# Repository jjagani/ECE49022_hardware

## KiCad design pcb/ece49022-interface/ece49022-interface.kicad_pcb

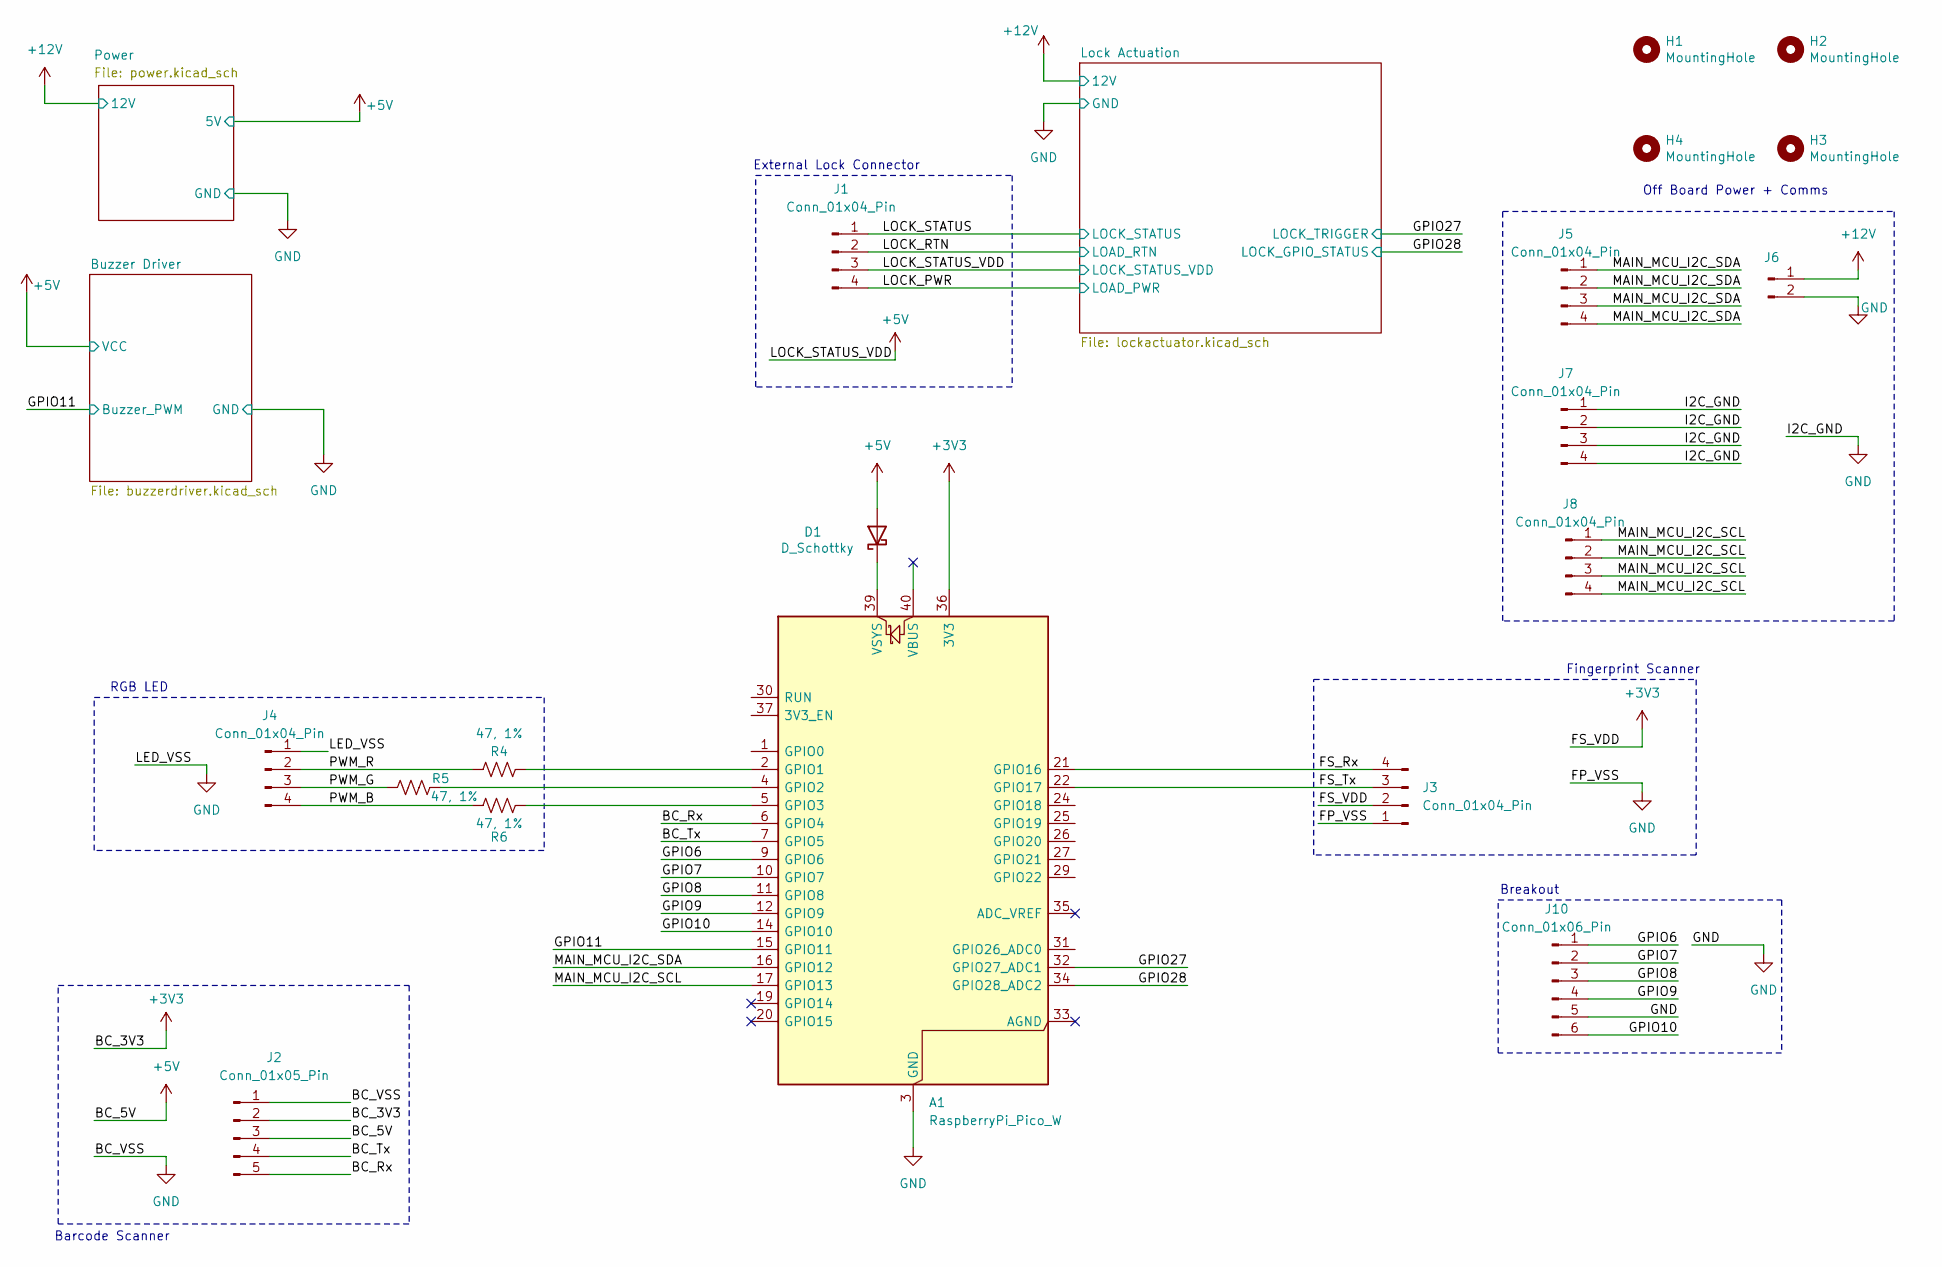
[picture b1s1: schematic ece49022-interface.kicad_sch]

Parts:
A1: RaspberryPi_Pico_W; RaspberryPi_Pico_W_SMD_HandSolder
D1: D_Schottky; D_2114_3652Metric_Pad1.85x3.75mm_HandSolder
H1, H2, H3, H4: MountingHole; MountingHole_2.7mm_M2.5
J1, J3, J4, J5, J7, J8: Conn_01x04_Pin; PinHeader_1x04_P2.54mm_Vertical
J2: Conn_01x05_Pin; PinHeader_1x05_P2.54mm_Vertical
J6: Conn_01x02_Pin; PinHeader_1x02_P2.54mm_Vertical
J10: Conn_01x06_Pin; PinHeader_1x06_P2.54mm_Vertical
R4, R5, R6: 47, 1%; R_0402_1005Metric_Pad0.72x0.64mm_HandSolder

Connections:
+3V3: A1.36 (3V3), J2.2, J3.2
+5V: D1.2 (A), J1.3, J2.3; also elsewhere on the board
+12V: J1.4, J6.1; also elsewhere on the board
/BC_Rx: A1.6 (GPIO4), J2.5
/BC_Tx: A1.7 (GPIO5), J2.4
/FS_Rx: A1.21 (GPIO16), J3.4
/FS_Tx: A1.22 (GPIO17), J3.3
/GPIO6: A1.9 (GPIO6), J10.1
/GPIO7: A1.10 (GPIO7), J10.2
/GPIO8: A1.11 (GPIO8), J10.3
/GPIO9: A1.12 (GPIO9), J10.4
/GPIO10: A1.14 (GPIO10), J10.6
/GPIO11: A1.15 (GPIO11); also elsewhere on the board
/GPIO27: A1.32 (GPIO27_ADC1); also elsewhere on the board
/GPIO28: A1.34 (GPIO28_ADC2); also elsewhere on the board
/LOCK_RTN: J1.2; also elsewhere on the board
/LOCK_STATUS: J1.1; also elsewhere on the board
/MAIN_MCU_I2C_SCL: A1.17 (GPIO13), J8.1, J8.2, J8.3, J8.4
/MAIN_MCU_I2C_SDA: A1.16 (GPIO12), J5.1, J5.2, J5.3, J5.4
/PWM_B: J4.4, R6.1
/PWM_G: J4.3, R5.1
/PWM_R: J4.2, R4.1
GND: A1.3 (GND), A1.8 (GND), A1.13 (GND), A1.18 (GND), A1.23 (GND), A1.28 (GND), A1.38 (GND), J2.1, J3.1, J4.1, J6.2, J7.1, J7.2, J7.3, J7.4, J10.5; also elsewhere on the board
unnamed: A1.2 (GPIO1), R4.2
unnamed: A1.4 (GPIO2), R5.2
unnamed: A1.5 (GPIO3), R6.2
unnamed: A1.39 (VSYS), D1.1 (K)

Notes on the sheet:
External Lock Connector
Fingerprint Scanner
Off Board Power + Comms
RGB LED
Barcode Scanner
Breakout

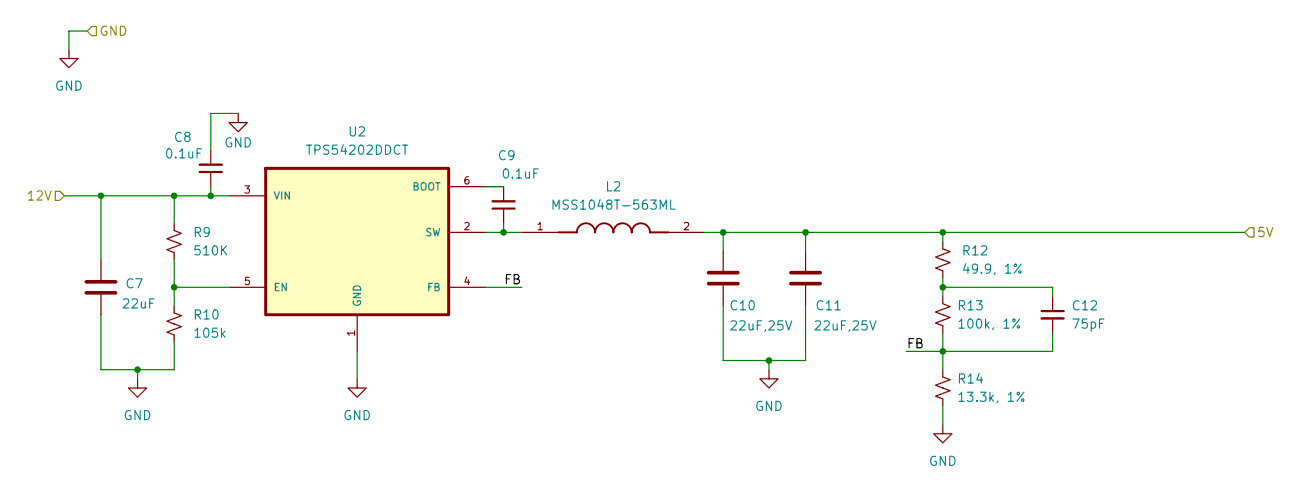
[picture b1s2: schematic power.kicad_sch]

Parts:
C7: 22uF; C_1206_3216Metric
C8, C9: 0.1uF; C_0402_1005Metric
C10, C11: 22uF,25V; C_0805_2012Metric_Pad1.18x1.45mm_HandSolder
C12: 75pF; C_0402_1005Metric
L2: MSS1048T-563ML; IND_MSS1048; PARTREV 02/16/22
R9: 510K; C_0402_1005Metric
R10: 105k; C_0402_1005Metric
R12: 49.9, 1%; C_0402_1005Metric
R13: 100k, 1%; C_0402_1005Metric
R14: 13.3k, 1%; C_0402_1005Metric
U2: TPS54202DDCT; TPS54202

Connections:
+5V: C10.1, C11.1, L2.2, R12.1; also elsewhere on the board
+12V: C7.1, C8.1, R9.1, U2.3 (VIN); also elsewhere on the board
/Power/FB: C12.2, R13.2, R14.1, U2.4 (FB)
GND: C7.2, C8.2, C10.2, C11.2, R10.2, R14.2, U2.1 (GND); also elsewhere on the board
unnamed: C12.1, R12.2, R13.1
unnamed: C9.2, U2.6 (BOOT)
unnamed: R9.2, R10.1, U2.5 (EN)
unnamed: C9.1, L2.1, U2.2 (SW)

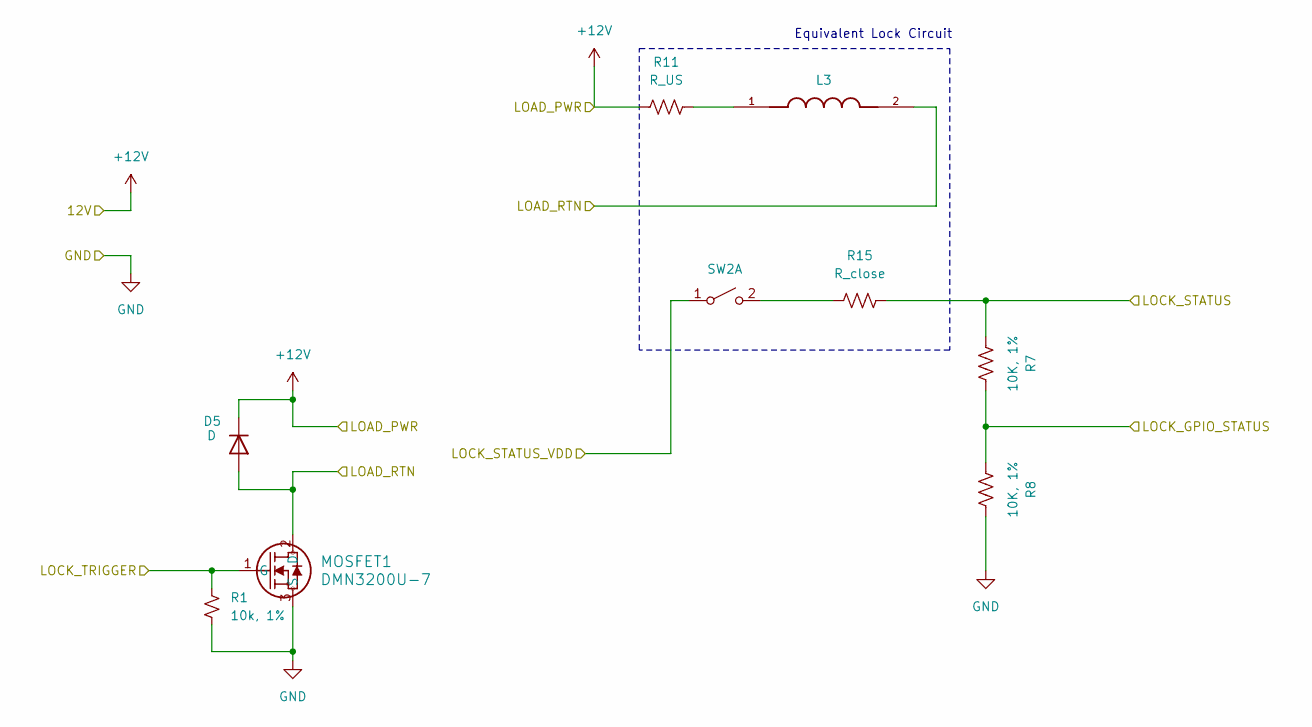
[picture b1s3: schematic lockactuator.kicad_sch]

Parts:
D5: D; SMFDO-219AB_VIS-L
L3: MSS1048T-563ML; PARTREV 02/16/22
MOSFET1: DMN3200U-7; SOT23_DMN3200U_2P9X1P3_DIO-L
R1: 10k, 1%; R_0402_1005Metric_Pad0.72x0.64mm_HandSolder
R7, R8: 10K, 1%; R_0402_1005Metric_Pad0.72x0.64mm_HandSolder
R11: R_US
R15: R_close
SW2: SW_DPST_x2

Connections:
+12V: D5.1 (K), R11.1; also elsewhere on the board
/GPIO27: MOSFET1.1 (G), R1.1; also elsewhere on the board
/GPIO28: R7.2, R8.1; also elsewhere on the board
/LOCK_RTN: D5.2 (A), L3.2, MOSFET1.2 (D); also elsewhere on the board
/LOCK_STATUS: R7.1, R15.2; also elsewhere on the board
GND: MOSFET1.3 (S), R1.2, R8.2; also elsewhere on the board
unnamed: L3.1, R11.2
unnamed: R15.1, SW2.2 (B)

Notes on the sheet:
Equivalent Lock Circuit

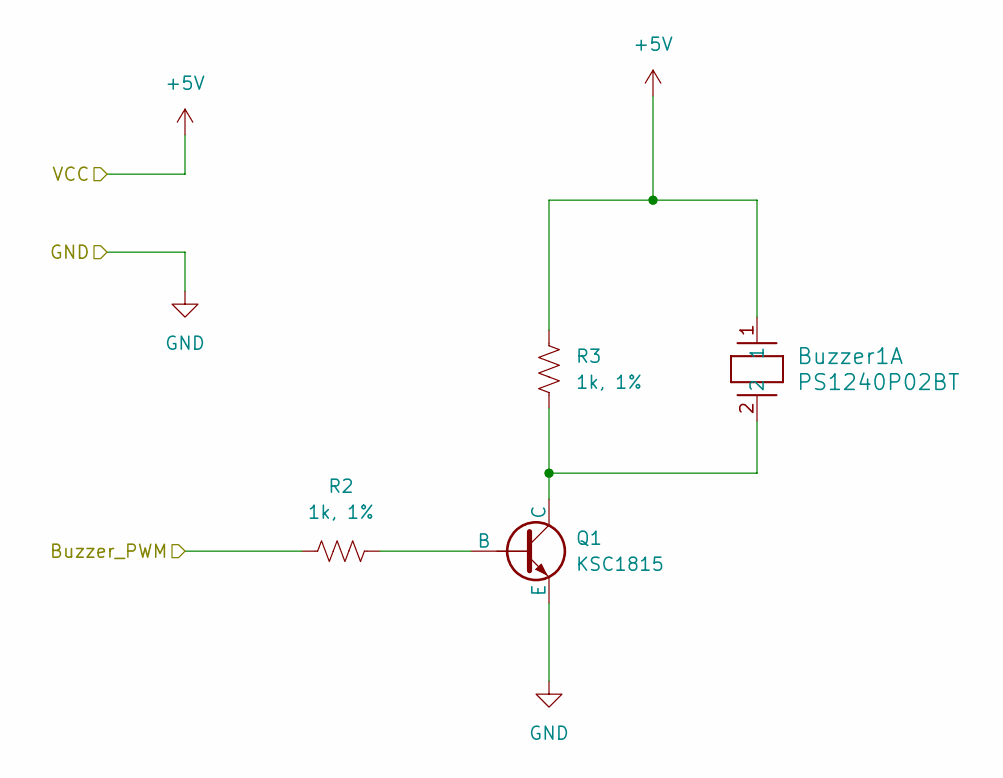
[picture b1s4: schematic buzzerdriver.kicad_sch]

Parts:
Buzzer1: PS1240P02BT; Buzzer_TDK_PS1240P02BT_D12.2mm_H6.5mm
Q1: KSC1815; TO-92L_Inline_Wide
R2, R3: 1k, 1%; R_0402_1005Metric_Pad0.72x0.64mm_HandSolder

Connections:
+5V: Buzzer1.1, R3.2; also elsewhere on the board
/GPIO11: R2.1; also elsewhere on the board
GND: Q1.3 (E); also elsewhere on the board
unnamed: Q1.2 (B), R2.2
unnamed: Buzzer1.2, Q1.1 (C), R3.1

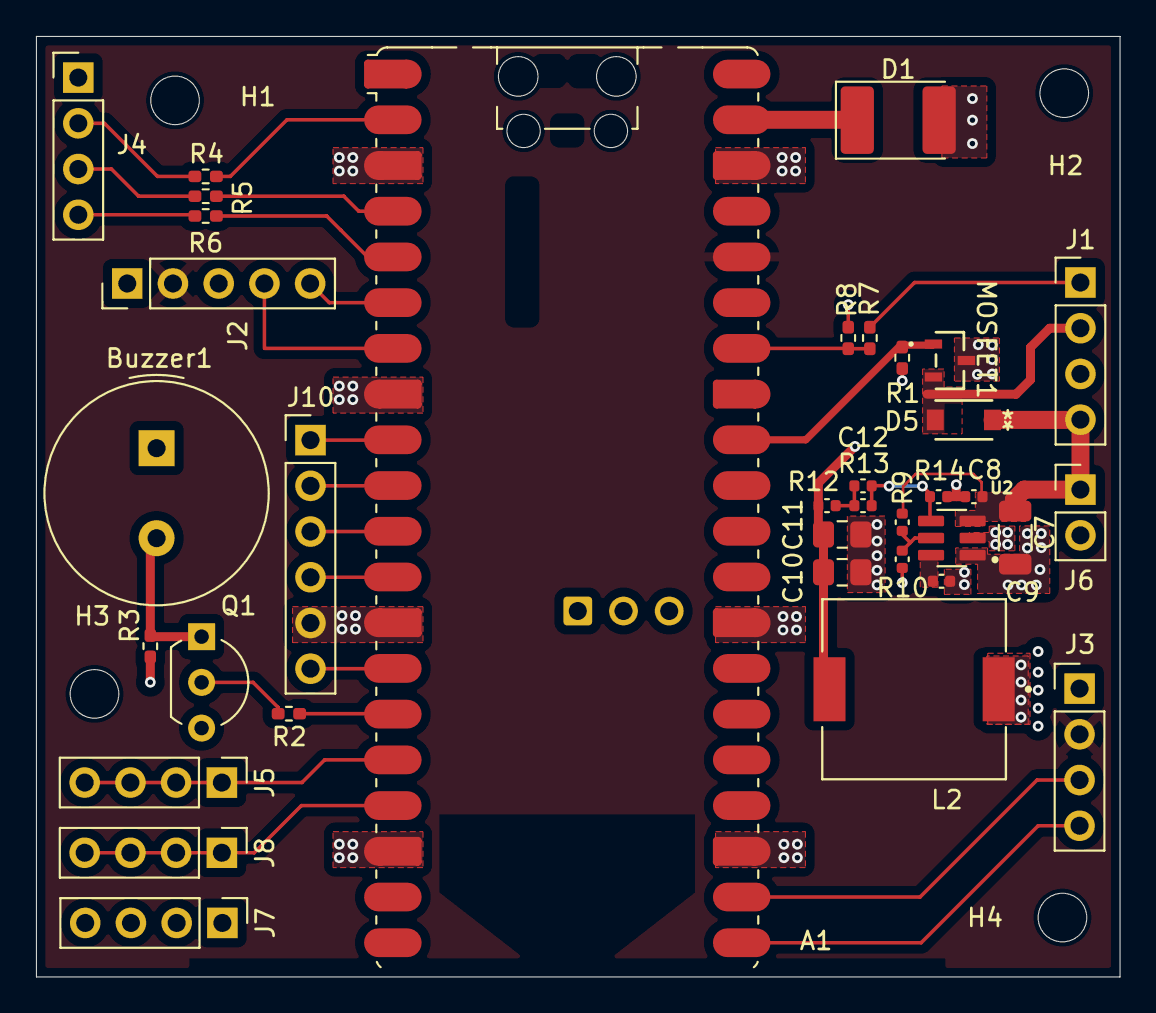
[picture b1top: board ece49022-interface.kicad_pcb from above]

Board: 4 copper layers, 60.2 x 52.2 mm, 40 parts (0 on the bottom side), 34 nets.

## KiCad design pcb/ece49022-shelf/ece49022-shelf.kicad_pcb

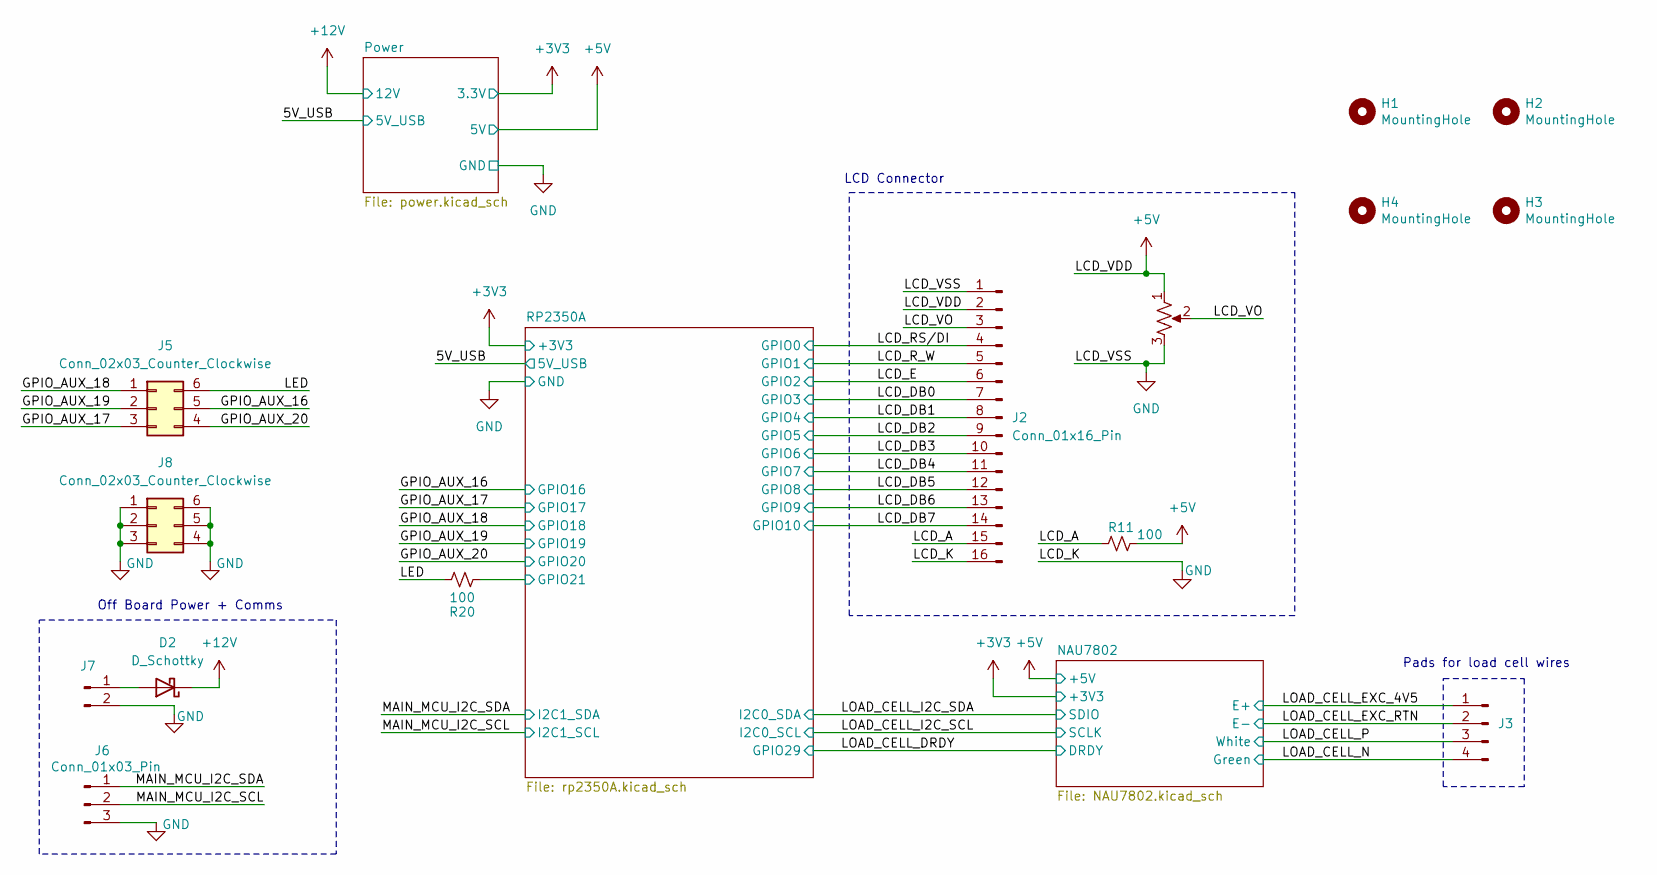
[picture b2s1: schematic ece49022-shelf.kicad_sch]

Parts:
D2: D_Schottky; SMFDO-219AB_VIS-L
H1, H2, H3, H4: MountingHole; MountingHole_2.7mm_M2.5
J2: Conn_01x16_Pin; PinSocket_1x16_P2.54mm_Vertical
J3: Conn_01x04_Pin; PinHeader_1x04_P2.54mm_Vertical
J5, J8: Conn_02x03_Counter_Clockwise; PinHeader_2x03_P2.54mm_Vertical
J6: Conn_01x03_Pin; PinHeader_1x03_P2.54mm_Vertical
J7: Conn_01x02_Pin; PinHeader_1x02_P2.54mm_Vertical
R11: 100; R_0805_2012Metric_Pad1.20x1.40mm_HandSolder
R20: 100; R_0603_1608Metric
RV1: R_Potentiometer_US; RES_C01R00

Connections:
+5V: J2.2, R11.2, RV1.1; also elsewhere on the board
+12V: D2.1 (K); also elsewhere on the board
/GPIO_AUX_16: J5.5; also elsewhere on the board
/GPIO_AUX_17: J5.3; also elsewhere on the board
/GPIO_AUX_18: J5.1; also elsewhere on the board
/GPIO_AUX_19: J5.2; also elsewhere on the board
/GPIO_AUX_20: J5.4; also elsewhere on the board
/LCD_A: J2.15, R11.1
/LCD_DB0: J2.7; also elsewhere on the board
/LCD_DB1: J2.8; also elsewhere on the board
/LCD_DB2: J2.9; also elsewhere on the board
/LCD_DB3: J2.10; also elsewhere on the board
/LCD_DB4: J2.11; also elsewhere on the board
/LCD_DB5: J2.12; also elsewhere on the board
/LCD_DB6: J2.13; also elsewhere on the board
/LCD_DB7: J2.14; also elsewhere on the board
/LCD_E: J2.6; also elsewhere on the board
/LCD_RS/DI: J2.4; also elsewhere on the board
/LCD_R_W: J2.5; also elsewhere on the board
/LCD_VO: J2.3, RV1.2
/LED: J5.6, R20.1
/LOAD_CELL_N: J3.4; also elsewhere on the board
/LOAD_CELL_P: J3.3; also elsewhere on the board
/MAIN_MCU_I2C_SCL: J6.2; also elsewhere on the board
/MAIN_MCU_I2C_SDA: J6.1; also elsewhere on the board
/RP2350A/GPIO21: R20.2; also elsewhere on the board
AVDD: J3.1; also elsewhere on the board
GND: J2.1, J2.16, J3.2, J6.3, J7.2, J8.1, J8.2, J8.3, J8.4, J8.5, J8.6, RV1.3; also elsewhere on the board
unnamed: D2.2 (A), J7.1

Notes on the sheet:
LCD Connector
Off Board Power + Comms
Pads for load cell wires

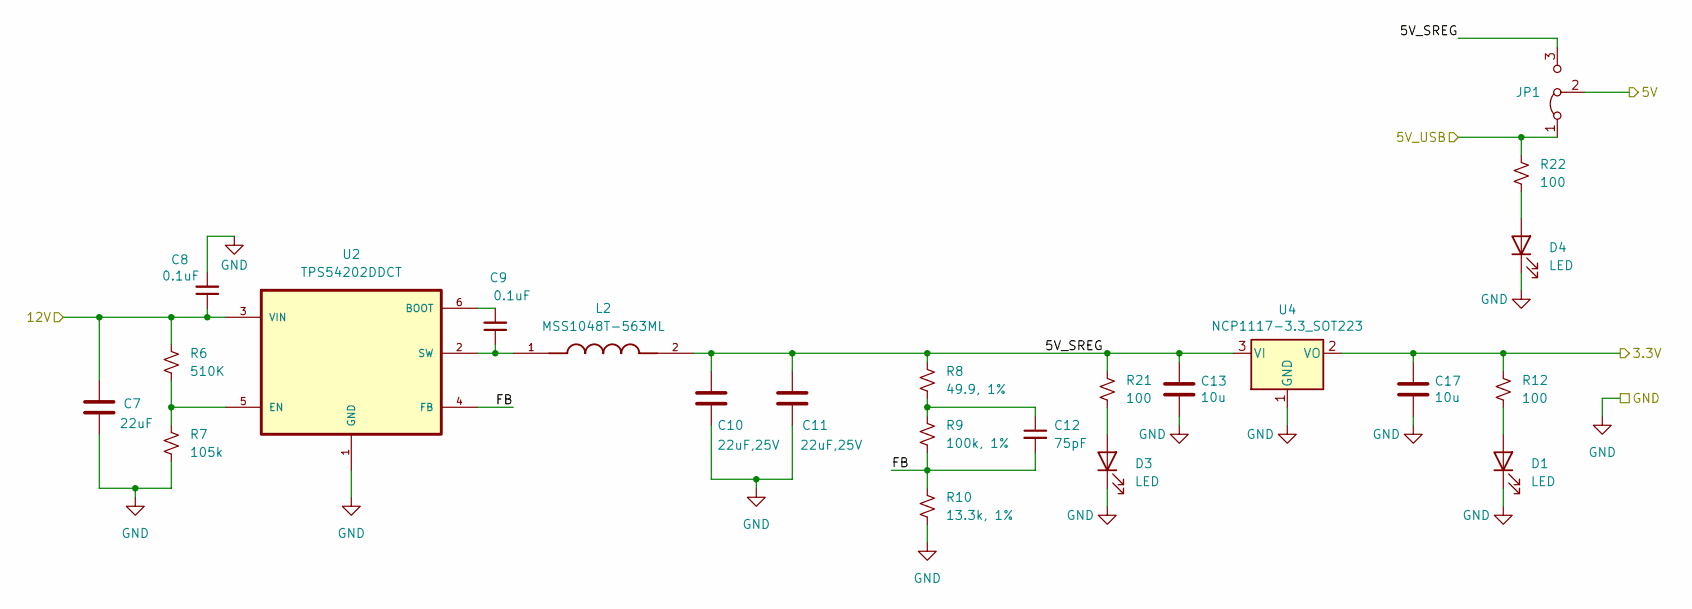
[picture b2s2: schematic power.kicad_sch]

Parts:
C7: 22uF; C_1206_3216Metric
C8, C9: 0.1uF; C_0402_1005Metric
C10, C11: 22uF,25V; C_0805_2012Metric_Pad1.18x1.45mm_HandSolder
C12: 75pF; C_0402_1005Metric
C13, C17: 10u; C_0805_2012Metric
D1, D3, D4: LED; R_0603_1608Metric
JP1: Jumper_3_Bridged12; PinHeader_1x03_P2.54mm_Vertical
L2: MSS1048T-563ML; IND_MSS1048; PARTREV 02/16/22
R6: 510K; C_0402_1005Metric
R7: 105k; C_0402_1005Metric
R8: 49.9, 1%; C_0402_1005Metric
R9: 100k, 1%; C_0402_1005Metric
R10: 13.3k, 1%; C_0402_1005Metric
R12, R21, R22: 100; R_0603_1608Metric
U2: TPS54202DDCT; TPS54202
U4: NCP1117-3.3_SOT223; SOT-223-3_TabPin2

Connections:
+3V3: C17.1, R12.1, U4.2 (VO); also elsewhere on the board
+5V: JP1.2 (C); also elsewhere on the board
+12V: C7.1, C8.1, R6.1, U2.3 (VIN); also elsewhere on the board
/5V_USB: JP1.1 (A), R22.1; also elsewhere on the board
/Power/5V_SREG: C10.1, C11.1, C13.1, JP1.3 (B), L2.2, R8.1, R21.1, U4.3 (VI)
/Power/FB: C12.2, R9.2, R10.1, U2.4 (FB)
GND: C7.2, C8.2, C10.2, C11.2, C13.2, C17.2, D1.1 (K), D3.1 (K), D4.1 (K), R7.2, R10.2, U2.1 (GND), U4.1 (GND); also elsewhere on the board
unnamed: C12.1, R8.2, R9.1
unnamed: D1.2 (A), R12.2
unnamed: D3.2 (A), R21.2
unnamed: D4.2 (A), R22.2
unnamed: C9.2, U2.6 (BOOT)
unnamed: R6.2, R7.1, U2.5 (EN)
unnamed: C9.1, L2.1, U2.2 (SW)

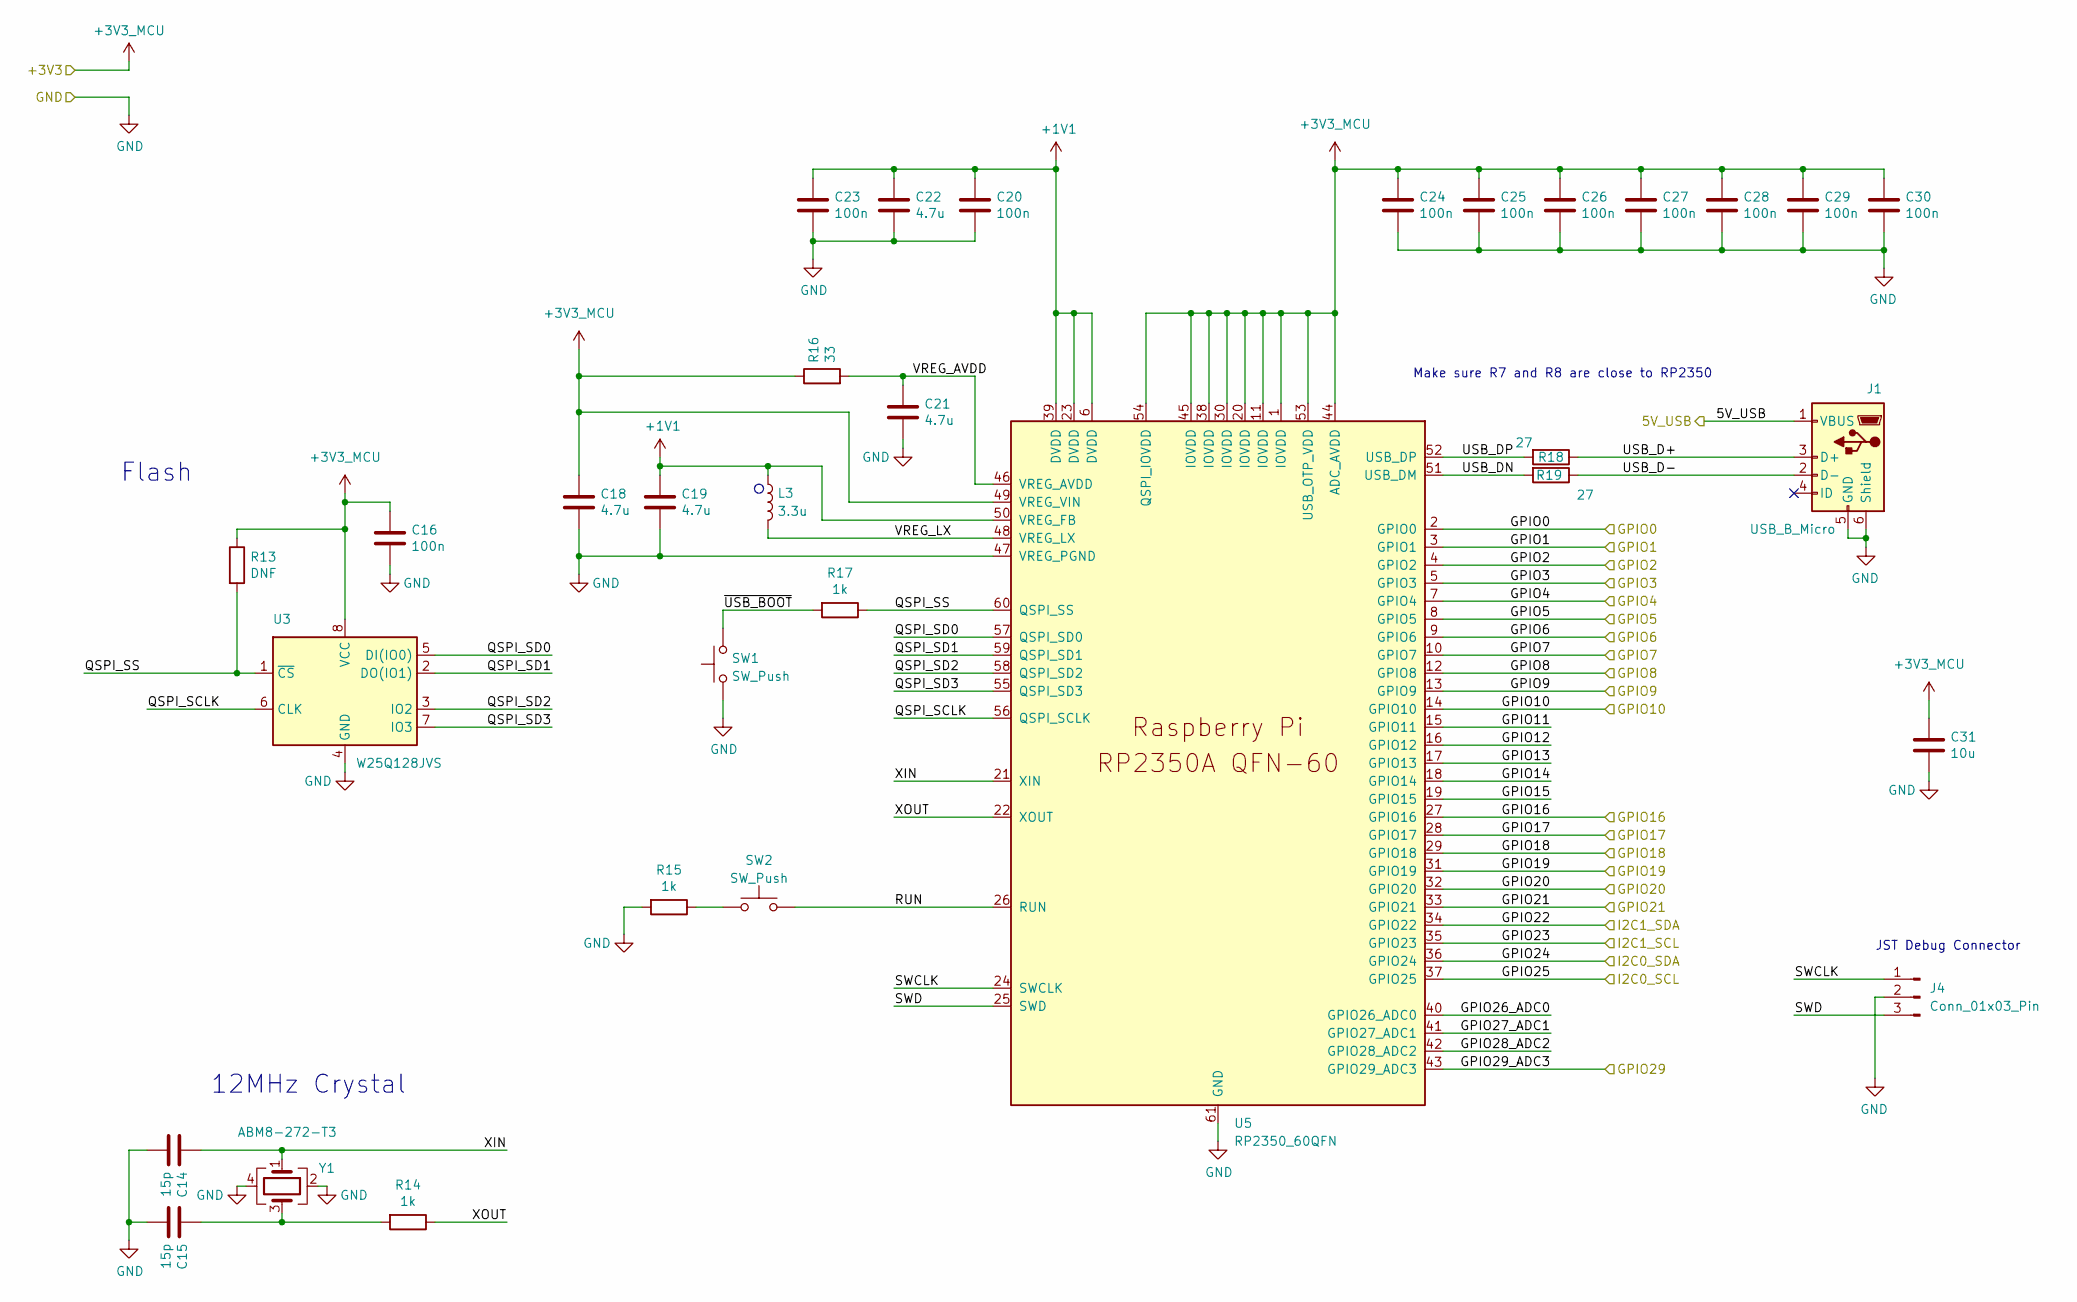
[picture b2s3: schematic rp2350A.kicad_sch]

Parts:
C14, C15: 15p; C_0402_1005Metric
C16: 100n; C_0402_1005Metric
C18, C19: 4.7u; C_0402_1005Metric_small_pads
C20, C23, C24, C25, C26, C27, C28, C29, C30: 100n; C_0402_1005Metric_Pad0.74x0.62mm_HandSolder
C21, C22: 4.7u; C_0402_1005Metric_Pad0.74x0.62mm_HandSolder
C31: 10u; C_0805_2012Metric
J1: USB_B_Micro; USB_Micro-B_Amphenol_10103594-0001LF_Horizontal_modified
J4: Conn_01x03_Pin; PinHeader_1x03_P2.54mm_Vertical
L3: 3.3u; L_pol_2016
R13: DNF; R_0402_1005Metric
R14: 1k; R_0402_1005Metric_Pad0.72x0.64mm_HandSolder
R15, R17: 1k; R_0402_1005Metric
R16: 33; R_0402_1005Metric_Pad0.72x0.64mm_HandSolder
R18, R19: 27; R_0402_1005Metric
SW1, SW2: SW_Push; SW_Push_1P1T_NO_Vertical_Wuerth_434133025816
U3: W25Q128JVS; SOIC-8_5.3x5.3mm_P1.27mm
U5: RP2350_60QFN; RP2350-QFN-60-1EP_7x7_P0.4mm_EP3.4x3.4mm_ThermalVias
Y1: ABM8-272-T3; Crystal_SMD_3225-4Pin_3.2x2.5mm

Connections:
+1V1: C19.1, C20.1, C22.1, C23.1, L3.1, U5.6 (DVDD), U5.23 (DVDD), U5.39 (DVDD), U5.50 (VREG_FB)
+3V3: C16.1, C18.1, C24.1, C25.1, C26.1, C27.1, C28.1, C29.1, C30.1, C31.1, R13.1, R16.1, U3.8 (VCC), U5.1 (IOVDD), U5.11 (IOVDD), U5.20 (IOVDD), U5.30 (IOVDD), U5.38 (IOVDD), U5.44 (ADC_AVDD), U5.45 (IOVDD), U5.49 (VREG_VIN), U5.53 (USB_OTP_VDD), U5.54 (QSPI_IOVDD); also elsewhere on the board
/5V_USB: J1.1 (VBUS); also elsewhere on the board
/GPIO_AUX_16: U5.27 (GPIO16); also elsewhere on the board
/GPIO_AUX_17: U5.28 (GPIO17); also elsewhere on the board
/GPIO_AUX_18: U5.29 (GPIO18); also elsewhere on the board
/GPIO_AUX_19: U5.31 (GPIO19); also elsewhere on the board
/GPIO_AUX_20: U5.32 (GPIO20); also elsewhere on the board
/LCD_DB0: U5.5 (GPIO3); also elsewhere on the board
/LCD_DB1: U5.7 (GPIO4); also elsewhere on the board
/LCD_DB2: U5.8 (GPIO5); also elsewhere on the board
/LCD_DB3: U5.9 (GPIO6); also elsewhere on the board
/LCD_DB4: U5.10 (GPIO7); also elsewhere on the board
/LCD_DB5: U5.12 (GPIO8); also elsewhere on the board
/LCD_DB6: U5.13 (GPIO9); also elsewhere on the board
/LCD_DB7: U5.14 (GPIO10); also elsewhere on the board
/LCD_E: U5.4 (GPIO2); also elsewhere on the board
/LCD_RS/DI: U5.2 (GPIO0); also elsewhere on the board
/LCD_R_W: U5.3 (GPIO1); also elsewhere on the board
/LOAD_CELL_DRDY: U5.43 (GPIO29_ADC3); also elsewhere on the board
/LOAD_CELL_I2C_SCL: U5.37 (GPIO25); also elsewhere on the board
/LOAD_CELL_I2C_SDA: U5.36 (GPIO24); also elsewhere on the board
/MAIN_MCU_I2C_SCL: U5.35 (GPIO23); also elsewhere on the board
/MAIN_MCU_I2C_SDA: U5.34 (GPIO22); also elsewhere on the board
/RP2350A/GPIO11: U5.15 (GPIO11)
/RP2350A/GPIO12: U5.16 (GPIO12)
/RP2350A/GPIO13: U5.17 (GPIO13)
/RP2350A/GPIO14: U5.18 (GPIO14)
/RP2350A/GPIO15: U5.19 (GPIO15)
/RP2350A/GPIO21: U5.33 (GPIO21); also elsewhere on the board
/RP2350A/GPIO26_ADC0: U5.40 (GPIO26_ADC0)
/RP2350A/GPIO27_ADC1: U5.41 (GPIO27_ADC1)
/RP2350A/GPIO28_ADC2: U5.42 (GPIO28_ADC2)
/RP2350A/QSPI_SCLK: U3.6 (CLK), U5.56 (QSPI_SCLK)
/RP2350A/QSPI_SD0: U3.5 (DI(IO0)), U5.57 (QSPI_SD0)
/RP2350A/QSPI_SD1: U3.2 (DO(IO1)), U5.59 (QSPI_SD1)
/RP2350A/QSPI_SD2: U3.3 (IO2), U5.58 (QSPI_SD2)
/RP2350A/QSPI_SD3: U3.7 (IO3), U5.55 (QSPI_SD3)
/RP2350A/QSPI_SS: R13.2, R17.1, U3.1 (~CS), U5.60 (QSPI_SS)
/RP2350A/RUN: SW2.2, U5.26 (RUN)
/RP2350A/SWCLK: J4.1, U5.24 (SWCLK)
/RP2350A/SWD: J4.3, U5.25 (SWD)
/RP2350A/USB_D+: J1.3 (D+), R18.1
/RP2350A/USB_D-: J1.2 (D-), R19.1
/RP2350A/USB_DN: R19.2, U5.51 (USB_DM)
/RP2350A/USB_DP: R18.2, U5.52 (USB_DP)
/RP2350A/VREG_AVDD: C21.1, R16.2, U5.46 (VREG_AVDD)
/RP2350A/VREG_LX: L3.2, U5.48 (VREG_LX)
/RP2350A/XIN: C14.1, U5.21 (XIN), Y1.1
/RP2350A/XOUT: R14.1, U5.22 (XOUT)
/RP2350A/~USB_BOOT: R17.2, SW1.2
GND: C14.2, C15.2, C16.2, C18.2, C19.2, C20.2, C21.2, C22.2, C23.2, C24.2, C25.2, C26.2, C27.2, C28.2, C29.2, C30.2, C31.2, J1.5 (GND), J1.6 (Shield), J4.2, R15.2, SW1.1, U3.4 (GND), U5.47 (VREG_PGND), U5.61 (GND), Y1.2, Y1.4; also elsewhere on the board
unnamed: C15.1, R14.2, Y1.3
unnamed: R15.1, SW2.1

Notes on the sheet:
Flash
12MHz Crystal
Make sure R7 and R8 are close to RP2350
JST Debug Connector

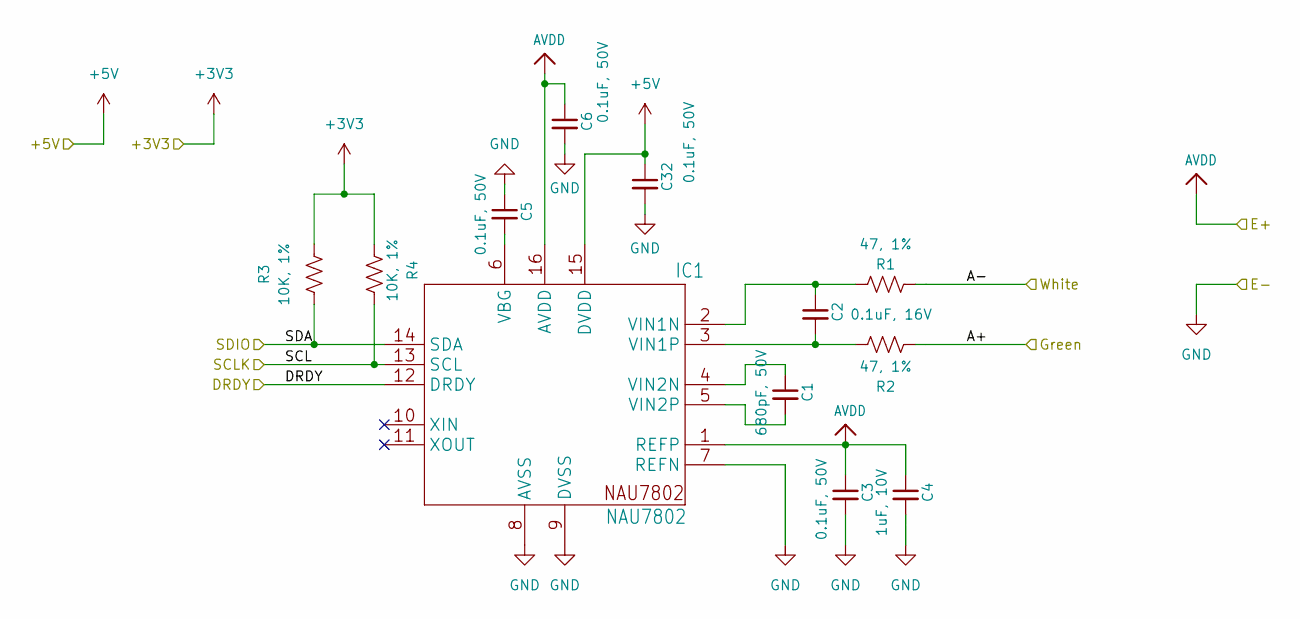
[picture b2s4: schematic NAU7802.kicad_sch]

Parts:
C1: 680pF, 50V; C_0402_1005Metric_Pad0.74x0.62mm_HandSolder
C2: 0.1uF, 16V; C_0402_1005Metric_Pad0.74x0.62mm_HandSolder
C3, C5, C6, C32: 0.1uF, 50V; C_0402_1005Metric_Pad0.74x0.62mm_HandSolder
C4: 1uF, 10V; C_0402_1005Metric_Pad0.74x0.62mm_HandSolder
IC1: NAU7802; SOI16_NAU7802SGI_NUV-M
R1, R2: 47, 1%; R_0402_1005Metric_Pad0.72x0.64mm_HandSolder
R3, R4: 10K, 1%; R_0402_1005Metric_Pad0.72x0.64mm_HandSolder

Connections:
+3V3: C32.1, IC1.15 (DVDD), R3.2, R4.2; also elsewhere on the board
/LOAD_CELL_DRDY: IC1.12 (DRDY); also elsewhere on the board
/LOAD_CELL_I2C_SCL: IC1.13 (SCL), R4.1; also elsewhere on the board
/LOAD_CELL_I2C_SDA: IC1.14 (SDA), R3.1; also elsewhere on the board
/LOAD_CELL_N: R2.2; also elsewhere on the board
/LOAD_CELL_P: R1.2; also elsewhere on the board
AVDD: C3.1, C4.1, C6.1, IC1.1 (REFP), IC1.16 (AVDD); also elsewhere on the board
GND: C3.2, C4.2, C5.1, C6.2, C32.2, IC1.7 (REFN), IC1.8 (AVSS), IC1.9 (DVSS); also elsewhere on the board
unnamed: C5.2, IC1.6 (VBG)
unnamed: C2.1, IC1.2 (VIN1N), R1.1
unnamed: C2.2, IC1.3 (VIN1P), R2.1
unnamed: C1.1, IC1.4 (VIN2N)
unnamed: C1.2, IC1.5 (VIN2P)

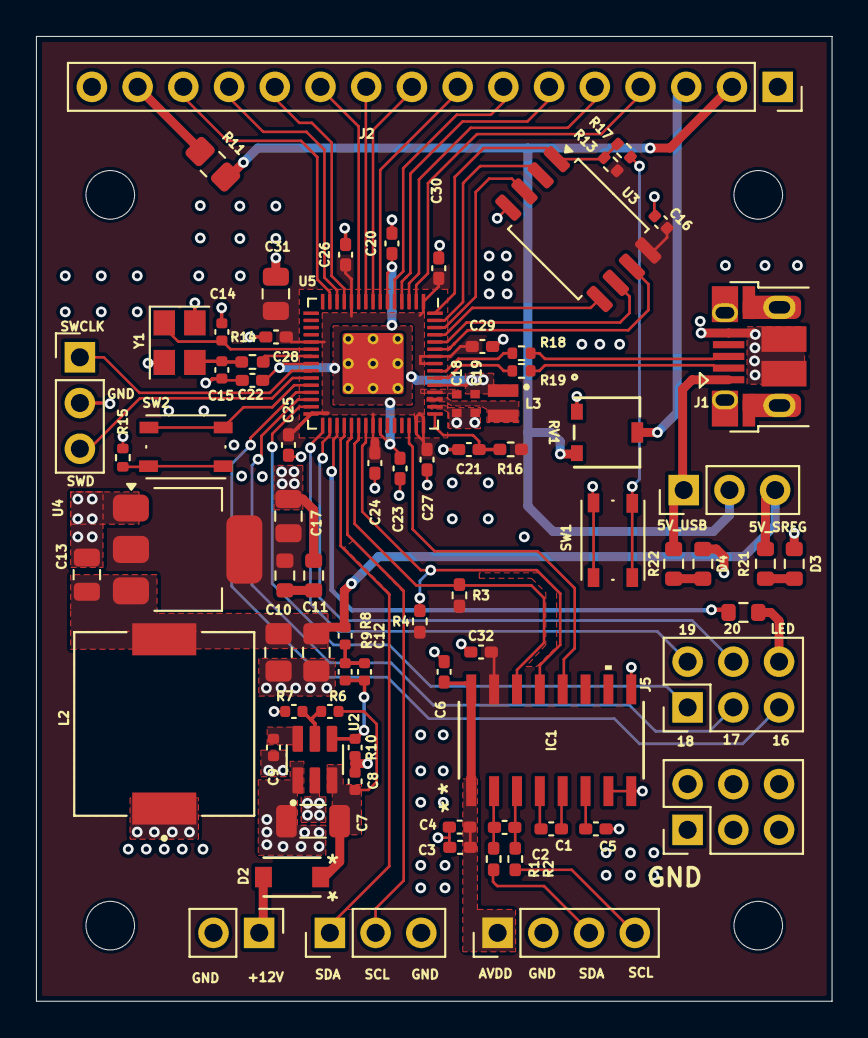
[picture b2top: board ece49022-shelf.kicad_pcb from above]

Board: 4 copper layers, 44.2 x 53.6 mm, 81 parts (0 on the bottom side), 69 nets.

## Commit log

2026-02-18 Shelf PCB Project Creation
2026-02-19 libraries added
2026-02-19 progress save
    working on 12V -> 5V converter
2026-02-19 Initial Power Schematics Finished
2026-02-19 fixed lib path
2026-02-19 paths fixed?
2026-02-19 Create NAU7802.sch
    added in nau7802
2026-02-19 rp2350A Added
2026-02-19 updated schematic
2026-02-20 Removed Breakout Board
2026-02-20 rp2350 inside
2026-02-20 Schematic
    update
2026-02-20 quicksave
2026-02-20 connecting top level
2026-02-20 added power
2026-02-20 stuff
2026-02-20 updated toplevel
2026-02-20 Interface
2026-02-20 Revert "updated toplevel"
    This reverts commit c6c85dd64a5aa0ec06541e25e577560202f66e02.
2026-02-20 test
2026-02-20 create circuits
2026-02-20 Added LCD Pins
2026-02-20 added LCD and offboard connectors
2026-02-20 forgot to push some stuff
2026-02-20 Interface update
2026-02-20 lock shit
2026-02-20 save
2026-02-20 edited shelf power and added power for interface PCB
2026-02-20 Added components and got pcb layout imported
2026-02-21 ending ts for the night
2026-02-21 Buzzer
    Updated buzzer schematic
2026-02-22 barcode scanner
2026-02-22 Fingerprint Scanner
2026-02-25 added footprints
2026-02-25 updated footprints, pcb
2026-02-25 footprint update
2026-02-27 Started Layout
2026-03-02 working n board
2026-03-02 footprints
2026-03-02 update buzzer and led
2026-03-02 update footprint and part selection
2026-03-02 update resistor
2026-03-02 start layout and part selection of rp
2026-03-02 Initial Placement done
2026-03-03 cap footprints for MCU smps needed to change
2026-03-03 start pcb
2026-03-03 Add pin connectors
2026-03-03 Redid external pin connectors
2026-03-03 pcb in progress
2026-03-04 update for pcb
2026-03-04 prepared for fills
2026-03-04 prepared for fill
2026-03-04 routing
2026-03-04 final layout i think
2026-03-04 need to add traces
2026-03-04 edited nau7802 schem and changed pins for layout reasons
2026-03-05 more pcb routing
2026-03-07 working on stuff
2026-03-08 more routing
2026-03-09 Initial PCB
2026-03-09 done? i think
2026-03-09 done?
2026-03-09 oshkosh drc
2026-03-11 need to finish power
2026-03-13 need to figure out lock circuit
2026-03-13 lock state
2026-03-13 update power resistors, wiring
2026-03-13 new converter layout
2026-03-16 layout chanes
2026-03-16 added stuff
2026-03-16 no warnings
2026-03-16 Added cutout
2026-03-16 shelf is ready
2026-03-16 breakout pins
2026-03-16 fixed some stuff in interface and changed trace width for 50 ohm in shelf pcb
